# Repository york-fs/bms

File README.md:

# Battery Management System Segment Board

The distributed BMS segment board connects to a series string of 12 cells and can be queried over isolated I2C to sample
cell voltages and temperatures.

## Features

* **Isolated I2C Communication to the Master Board**
* **Accurate Voltage Measurement Using the MAX14920 Analog Frontend**
* **Passive Cell Balancing**
* **Up to 23 Connected Thermistors**
  * Three onboard thermistors around the cell balancers
  * Twenty external thermistors across two JST PUD connectors

## Cloning

A recursive clone must be used to download the `kicad-library` repository:

    git clone --recursive https://github.com/york-fs/bms-segment.git

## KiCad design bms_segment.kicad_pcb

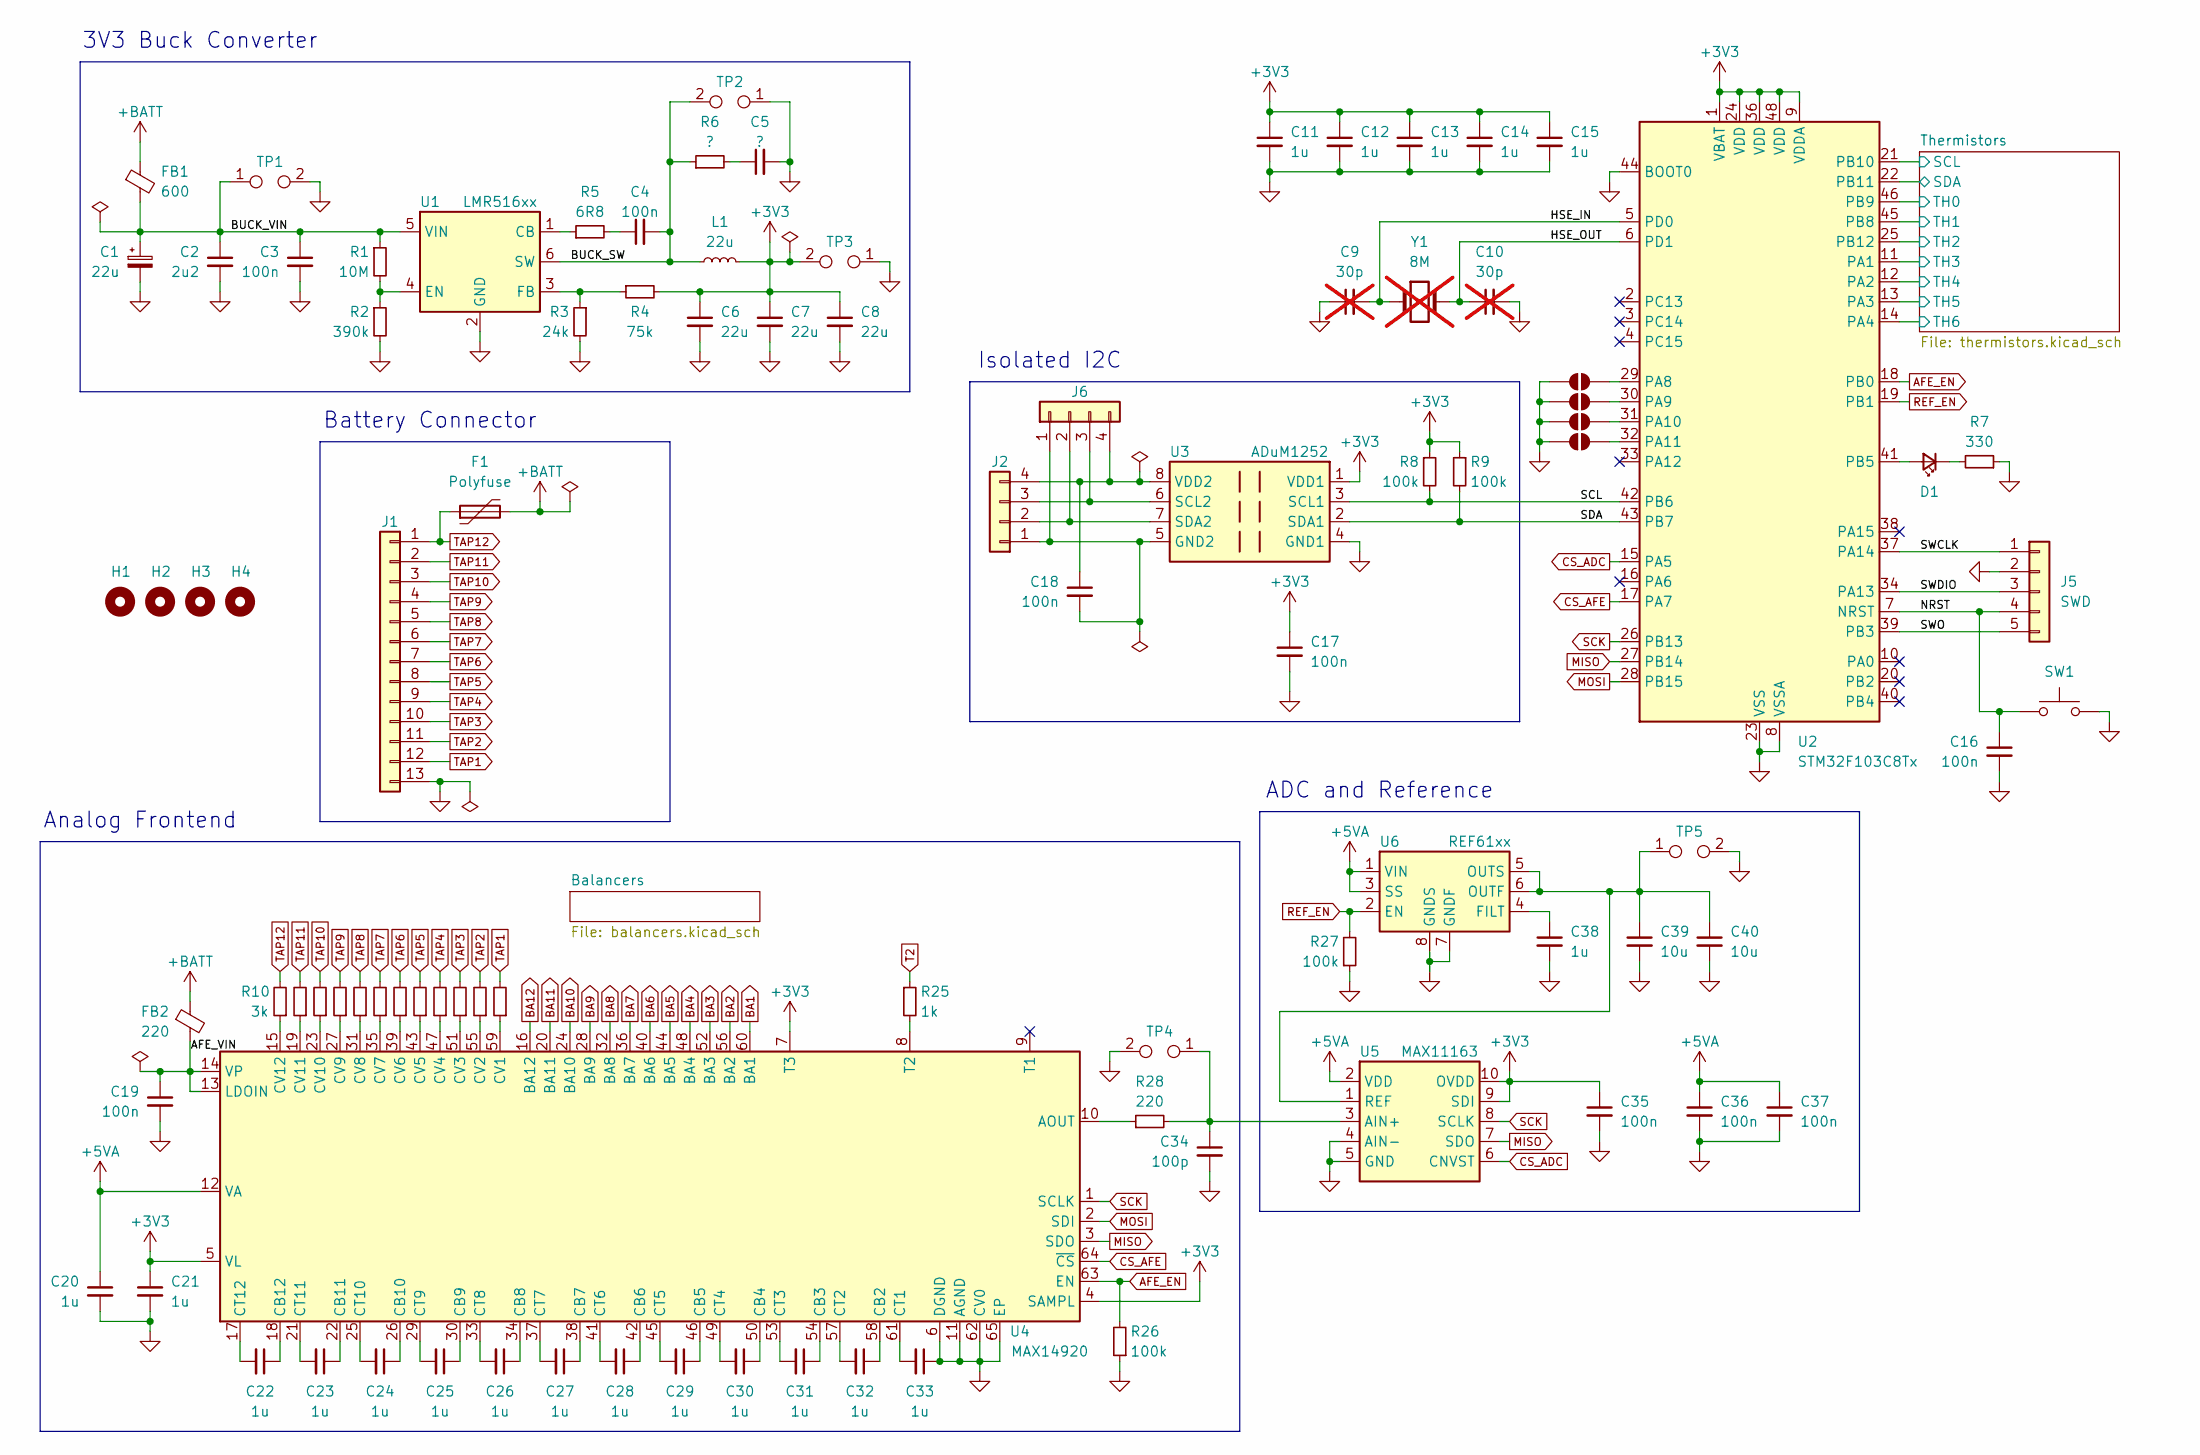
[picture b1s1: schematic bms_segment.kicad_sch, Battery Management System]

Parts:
C1: 22u; CP_Elec_6.3x7.7; Mfr # EEEFK1J220XP
C2: 2u2; C_1210_3225Metric; Mfr # GRM32ER72A225KA35
C3, C19: 100n; C_1206_3216Metric; Mfr # GRM31C5C2A104JA01L
C4, C16, C17, C18, C35, C36, C37: 100n; C_0603_1608Metric; Mfr # CL10B104KB8NNNC
C5: ?; C_0603_1608Metric
C6, C7, C8: 22u; C_1210_3225Metric; Mfr # GRM32ER71E226KE15L
C9, C10: 30p; C_0603_1608Metric; Mfr # GQM1875C2E300GB12D; not fitted
C11, C12, C13, C14, C15, C20, C21, C38: 1u; C_0603_1608Metric; Mfr # CL10B105KB8NQNC
C22, C23, C24, C25, C26, C27, C28, C29, C30, C31, C32, C33: 1u; C_0805_2012Metric; Mfr # GCM21BR71H105KA03L
C34: 100p; C_0603_1608Metric
C39, C40: 10u; C_1206_3216Metric; Mfr # GRM31CR71C106KA12L
D1: LED_Small; LED_0603_1608Metric; Mfr # NCD0603R1
F1: Polyfuse; R_1206_3216Metric; Mfr # 1206L010/60WR
FB1: 600; L_0603_1608Metric; Mfr # BLM18KG601SN1D
FB2: 220; L_0603_1608Metric; Mfr # BLM18PG221SN1D
H1, H2, H3, H4: MountingHole; MountingHole_3.2mm_M3
J1: CELL_TAPS; PhoenixContact_MC_1,5_13-G-3.81_1x13_P3.81mm_Horizontal; Mfr # MX15EDGRC-3.81-13P-GN01-Cu-A
J2, J6: I2C; JST_PH_B4B-PH-K_1x04_P2.00mm_Vertical; Mfr # B4B-PH-K-S(LF)(SN)
J5: SWD; PinHeader_1x05_P2.54mm_Vertical
JP1, JP2, JP3, JP4: SolderJumper_2_Open; SolderJumper-2_P1.3mm_Open_RoundedPad1.0x1.5mm
L1: 22u; L_Vishay_IHLP-2525; Mfr # IHLP2525CZER220M1A
R1: 10M; R_0603_1608Metric
R2: 390k; R_0603_1608Metric
R3: 24k; R_0603_1608Metric
R4: 75k; R_0603_1608Metric
R5: 6R8; R_0603_1608Metric
R6: ?; R_0603_1608Metric
R7: 330; R_0603_1608Metric; Mfr # 0603WAF3300T5E
R8, R9, R26, R27: 100k; R_0603_1608Metric; Mfr # 0603WAF1003T5E
R10, R11, R12, R13, R14, R15, R16, R17, R18, R19, R20, R21: 3k; R_0603_1608Metric; Mfr # 0603WAF3001T5E
R25: 1k; R_0603_1608Metric; Mfr # 0603WAF1001T5E
R28: 220; R_0603_1608Metric
SW1: SW_Push; SW_Push_SPST_NO_Alps_SKRK; Mfr # TS-1088-AR02016
TP1, TP2, TP3, TP4, TP5: TestPoint_2Pole; TestPoint_2Pads_Pitch2.54mm_Drill1.0mm
U1: LMR516xx; SOT-23-6; Mfr # LMR51606XDBVR
U2: STM32F103C8Tx; LQFP-48_7x7mm_P0.5mm; Mfr # STM32F103C8T6
U3: ADuM1252; MSOP-8_3x3mm_P0.65mm; Mfr # ADUM1252AUA+
U4: MAX14920; TQFP-64-1EP_10x10mm_P0.5mm_EP5.305x5.305mm; Mfr # MAX14920ECB+
U5: MAX11163; MSOP-10_3x3mm_P0.5mm; Mfr # MAX11163EUB+
U6: REF61xx; VSSOP-8_3x3mm_P0.65mm; Mfr # REF6145IDGKT
Y1: 8M; Crystal_SMD_5032-2Pin_5.0x3.2mm; Mfr # X50328MSB2GI; not fitted

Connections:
+3V3: C6.1, C7.1, C8.1, C11.1, C12.1, C13.1, C14.1, C15.1, C17.1, C21.1, C35.1, L1.2, R4.2, R8.1, R9.1, TP3.2, U2.1 (VBAT), U2.9 (VDDA), U2.24 (VDD), U2.36 (VDD), U2.48 (VDD), U3.1 (VDD1), U4.4 (SAMPL), U4.5 (VL), U4.7 (T3), U5.9 (SDI), U5.10 (OVDD); also elsewhere on the board
+5VA: C20.1, C36.1, C37.1, U4.12 (VA), U5.2 (VDD), U6.1 (VIN), U6.3 (SS)
+BATT: F1.2, FB1.1, FB2.1
/AFE_VIN: C19.1, FB2.2, U4.13 (LDOIN), U4.14 (VP)
/BUCK_SW: C4.2, L1.1, R6.1, TP2.2, U1.6 (SW)
/BUCK_VIN: C1.1, C2.1, C3.1, FB1.2, R1.1, TP1.1, U1.5 (VIN)
/HSE_IN: C9.2, U2.5 (PD0), Y1.1
/HSE_OUT: C10.1, U2.6 (PD1), Y1.2
/NRST: C16.1, J5.4, SW1.1, U2.7 (NRST)
/SCL: R8.2, U2.42 (PB6), U3.3 (SCL1)
/SDA: R9.2, U2.43 (PB7), U3.2 (SDA1)
/SWCLK: J5.1, U2.37 (PA14)
/SWDIO: J5.3, U2.34 (PA13)
/SWO: J5.5, U2.39 (PB3)
/Thermistors/SCL: U2.21 (PB10); also elsewhere on the board
/Thermistors/SDA: U2.22 (PB11); also elsewhere on the board
/Thermistors/TH0: U2.46 (PB9); also elsewhere on the board
/Thermistors/TH1: U2.45 (PB8); also elsewhere on the board
/Thermistors/TH2: U2.25 (PB12); also elsewhere on the board
/Thermistors/TH3: U2.11 (PA1); also elsewhere on the board
/Thermistors/TH4: U2.12 (PA2); also elsewhere on the board
/Thermistors/TH5: U2.13 (PA3); also elsewhere on the board
/Thermistors/TH6: U2.14 (PA4); also elsewhere on the board
AFE_EN: R26.2, U2.18 (PB0), U4.63 (EN)
BA1: U4.60 (BA1); also elsewhere on the board
BA2: U4.56 (BA2); also elsewhere on the board
BA3: U4.52 (BA3); also elsewhere on the board
BA4: U4.48 (BA4); also elsewhere on the board
BA5: U4.44 (BA5); also elsewhere on the board
BA6: U4.40 (BA6); also elsewhere on the board
BA7: U4.36 (BA7); also elsewhere on the board
BA8: U4.32 (BA8); also elsewhere on the board
BA9: U4.28 (BA9); also elsewhere on the board
BA10: U4.24 (BA10); also elsewhere on the board
BA11: U4.20 (BA11); also elsewhere on the board
BA12: U4.16 (BA12); also elsewhere on the board
CS_ADC: U2.15 (PA5), U5.6 (CNVST)
CS_AFE: U2.17 (PA7), U4.64 (~CS)
GND: C1.2, C2.2, C3.2, C5.2, C6.2, C7.2, C8.2, C9.1, C10.2, C11.2, C12.2, C13.2, C14.2, C15.2, C16.2, C17.2, C19.2, C20.2, C21.2, C33.1, C34.2, C35.2, C36.2, C37.2, C38.2, C39.2, C40.2, J1.13, J5.2, JP1.1 (A), JP2.1 (A), JP3.1 (A), JP4.1 (A), R2.2, R3.2, R7.1, R26.1, R27.1, SW1.2, TP1.2, TP2.1, TP3.1, TP4.2, TP5.2, U1.2 (GND), U2.8 (VSSA), U2.23 (VSS), U2.35 (VSS), U2.44 (BOOT0), U2.47 (VSS), U3.4 (GND1), U4.6 (DGND), U4.11 (AGND), U4.62 (CV0), U4.65 (EP), U5.4 (AIN-), U5.5 (GND), U6.7 (GNDF), U6.8 (GNDS); also elsewhere on the board
MISO: U2.27 (PB14), U4.3 (SDO), U5.7 (SDO)
MOSI: U2.28 (PB15), U4.2 (SDI)
unnamed: C4.1, R5.2
unnamed: C5.1, R6.2
unnamed: D1.2 (A), U2.41 (PB5)
unnamed: D1.1 (K), R7.2
unnamed: C18.2, J2.1, J6.1, U3.5 (GND2)
unnamed: J2.2, J6.2, U3.7 (SDA2)
unnamed: J2.3, J6.3, U3.6 (SCL2)
unnamed: C18.1, J2.4, J6.4, U3.8 (VDD2)
unnamed: JP1.2 (B), U2.29 (PA8)
unnamed: JP2.2 (B), U2.30 (PA9)
unnamed: JP3.2 (B), U2.31 (PA10)
unnamed: JP4.2 (B), U2.32 (PA11)
unnamed: R5.1, U1.1 (CB)
unnamed: R1.2, R2.1, U1.4 (EN)
unnamed: R3.1, R4.1, U1.3 (FB)
unnamed: R28.1, U4.10 (AOUT)
unnamed: C32.1, U4.58 (CB2)
unnamed: C31.1, U4.54 (CB3)
unnamed: C30.1, U4.50 (CB4)
unnamed: C29.1, U4.46 (CB5)
unnamed: C28.1, U4.42 (CB6)
unnamed: C27.1, U4.38 (CB7)
unnamed: C26.1, U4.34 (CB8)
unnamed: C25.1, U4.30 (CB9)
unnamed: C24.1, U4.26 (CB10)
unnamed: C23.1, U4.22 (CB11)
unnamed: C22.1, U4.18 (CB12)
unnamed: C33.2, U4.61 (CT1)
unnamed: C32.2, U4.57 (CT2)
unnamed: C31.2, U4.53 (CT3)
unnamed: C30.2, U4.49 (CT4)
unnamed: C29.2, U4.45 (CT5)
unnamed: C28.2, U4.41 (CT6)
unnamed: C27.2, U4.37 (CT7)
unnamed: C26.2, U4.33 (CT8)
unnamed: C25.2, U4.29 (CT9)
unnamed: C24.2, U4.25 (CT10)
unnamed: C23.2, U4.21 (CT11)
unnamed: C22.2, U4.17 (CT12)
unnamed: R21.1, U4.59 (CV1)
unnamed: R20.1, U4.55 (CV2)
unnamed: R19.1, U4.51 (CV3)
unnamed: R18.1, U4.47 (CV4)
unnamed: R17.1, U4.43 (CV5)
unnamed: R16.1, U4.39 (CV6)
unnamed: R15.1, U4.35 (CV7)
unnamed: R14.1, U4.31 (CV8)
unnamed: R13.1, U4.27 (CV9)
unnamed: R12.1, U4.23 (CV10)
unnamed: R11.1, U4.19 (CV11)
unnamed: R10.1, U4.15 (CV12)
unnamed: R25.2, U4.8 (T2)
unnamed: C34.1, R28.2, TP4.1, U5.3 (AIN+)
unnamed: C39.1, C40.1, TP5.1, U5.1 (REF), U6.5 (OUTS), U6.6 (OUTF)
unnamed: C38.1, U6.4 (FILT)
REF_EN: R27.2, U2.19 (PB1), U6.2 (EN)
SCK: U2.26 (PB13), U4.1 (SCLK), U5.8 (SCLK)
T2: R25.1; also elsewhere on the board
TAP1: J1.12, R21.2; also elsewhere on the board
TAP2: J1.11, R20.2; also elsewhere on the board
TAP3: J1.10, R19.2; also elsewhere on the board
TAP4: J1.9, R18.2; also elsewhere on the board
TAP5: J1.8, R17.2; also elsewhere on the board
TAP6: J1.7, R16.2; also elsewhere on the board
TAP7: J1.6, R15.2; also elsewhere on the board
TAP8: J1.5, R14.2; also elsewhere on the board
TAP9: J1.4, R13.2; also elsewhere on the board
TAP10: J1.3, R12.2; also elsewhere on the board
TAP11: J1.2, R11.2; also elsewhere on the board
TAP12: F1.1, J1.1, R10.2; also elsewhere on the board

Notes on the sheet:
ADC and Reference
Isolated I2C
3V3 Buck Converter
Analog Frontend
Battery Connector

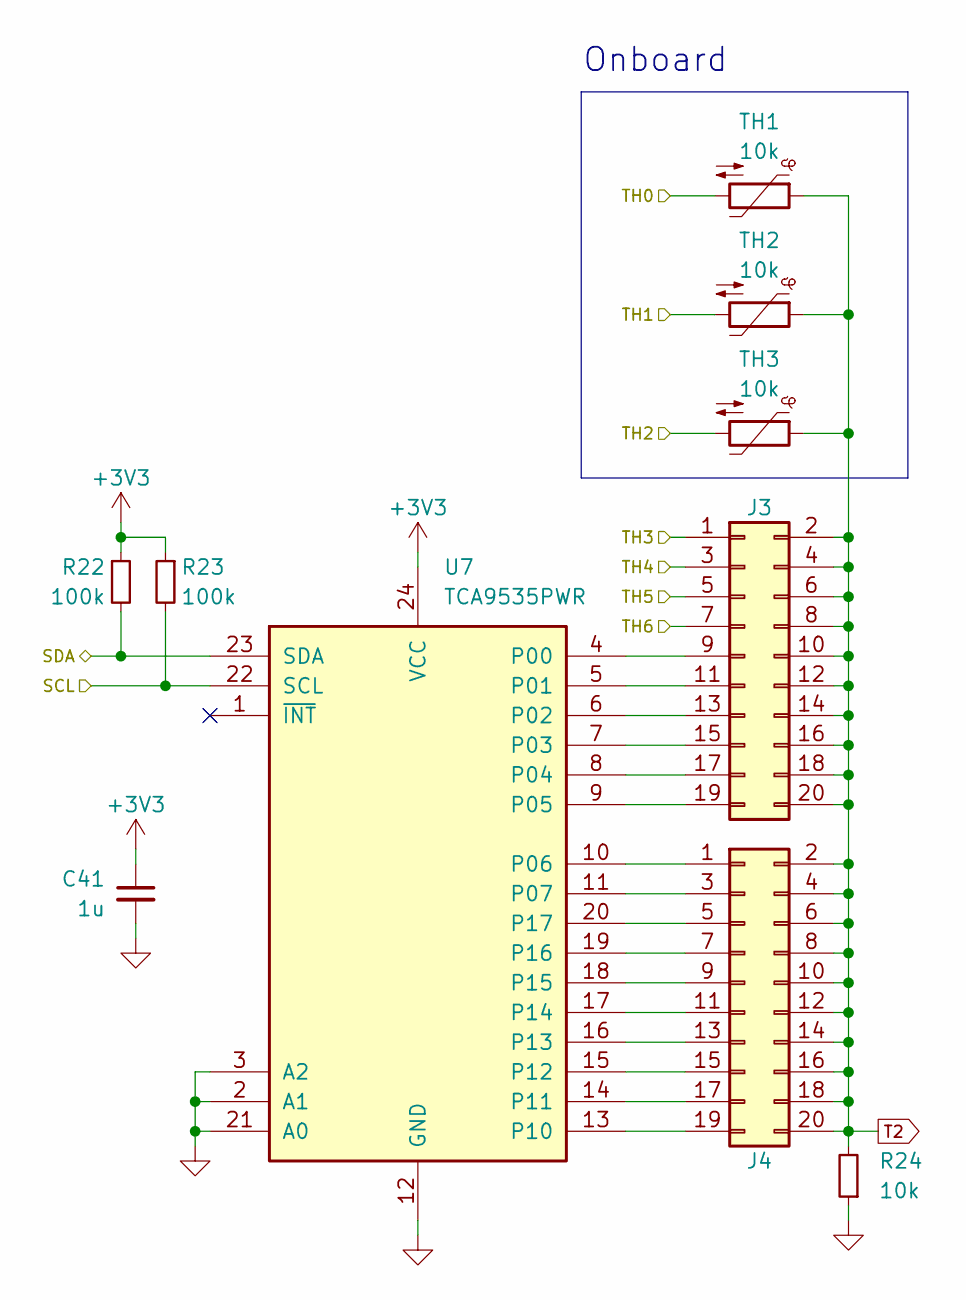
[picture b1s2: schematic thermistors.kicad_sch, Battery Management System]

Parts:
C41: 1u; C_0603_1608Metric; Mfr # CL10B105KB8NQNC
J3: THERM_1; JST_PUD_S20B-PUDSS-1_2x10_P2.00mm_Horizontal; Mfr # S20B-PUDSS-1(LF)(SN)
J4: THERM_2; JST_PUD_S20B-PUDSS-1_2x10_P2.00mm_Horizontal; Mfr # S20B-PUDSS-1(LF)(SN)
R22, R23: 100k; R_0603_1608Metric; Mfr # 0603WAF1003T5E
R24: 10k; R_0603_1608Metric; Mfr # 0603WAF1002T5E
TH1, TH2, TH3: 10k; R_0603_1608Metric; Mfr # NCP18XH103F03RB
U7: TCA9535PWR; TSSOP-24_4.4x7.8mm_P0.65mm; Mfr # TCA9535PWR

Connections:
+3V3: C41.1, R22.1, R23.1, U7.24 (VCC); also elsewhere on the board
/Thermistors/SCL: R23.2, U7.22 (SCL); also elsewhere on the board
/Thermistors/SDA: R22.2, U7.23 (SDA); also elsewhere on the board
/Thermistors/TH0: TH1.2; also elsewhere on the board
/Thermistors/TH1: TH2.2; also elsewhere on the board
/Thermistors/TH2: TH3.2; also elsewhere on the board
/Thermistors/TH3: J3.1; also elsewhere on the board
/Thermistors/TH4: J3.3; also elsewhere on the board
/Thermistors/TH5: J3.5; also elsewhere on the board
/Thermistors/TH6: J3.7; also elsewhere on the board
GND: C41.2, R24.1, U7.2 (A1), U7.3 (A2), U7.12 (GND), U7.21 (A0); also elsewhere on the board
unnamed: J3.9, U7.4 (P00)
unnamed: J3.11, U7.5 (P01)
unnamed: J3.13, U7.6 (P02)
unnamed: J3.15, U7.7 (P03)
unnamed: J3.17, U7.8 (P04)
unnamed: J3.19, U7.9 (P05)
unnamed: J4.1, U7.10 (P06)
unnamed: J4.3, U7.11 (P07)
unnamed: J4.5, U7.20 (P17)
unnamed: J4.7, U7.19 (P16)
unnamed: J4.9, U7.18 (P15)
unnamed: J4.11, U7.17 (P14)
unnamed: J4.13, U7.16 (P13)
unnamed: J4.15, U7.15 (P12)
unnamed: J4.17, U7.14 (P11)
unnamed: J4.19, U7.13 (P10)
T2: J3.2, J3.4, J3.6, J3.8, J3.10, J3.12, J3.14, J3.16, J3.18, J3.20, J4.2, J4.4, J4.6, J4.8, J4.10, J4.12, J4.14, J4.16, J4.18, J4.20, R24.2, TH1.1, TH2.1, TH3.1; also elsewhere on the board

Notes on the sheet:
Onboard

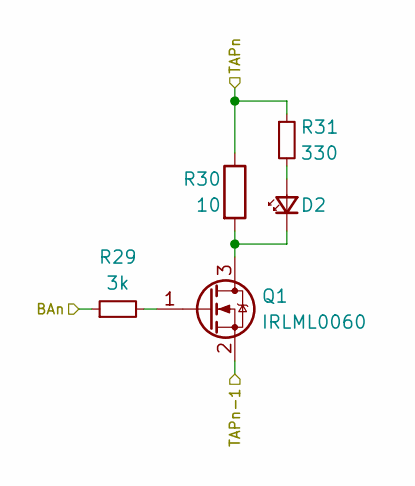
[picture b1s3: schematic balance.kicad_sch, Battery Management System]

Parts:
D2: LED_Small; LED_0603_1608Metric; Mfr # NCD0603R1
Q1: IRLML0060; SOT-23; Mfr # IRLML0060TRPBF
R29: 3k; R_0603_1608Metric; Mfr # 0603WAF3001T5E
R30: 10; R_2512_6332Metric; Mfr # RPL-12K10R0FT
R31: 330; R_0603_1608Metric; Mfr # 0603WAF3300T5E

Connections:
BA1: R29.1; also elsewhere on the board
GND: Q1.2 (S); also elsewhere on the board
unnamed: D2.2 (A), R31.2
unnamed: D2.1 (K), Q1.3 (D), R30.2
unnamed: Q1.1 (G), R29.2
TAP1: R30.1, R31.1; also elsewhere on the board

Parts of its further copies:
D3, D4, D5, D6, D7, D8, D9, D10, D11, D12, D13: LED_Small; LED_0603_1608Metric; Mfr # NCD0603R1
Q2, Q3, Q4, Q5, Q6, Q7, Q8, Q9, Q10, Q11, Q12: IRLML0060; SOT-23; Mfr # IRLML0060TRPBF
R32, R35, R38, R41, R44, R47, R50, R53, R56, R59, R62: 3k; R_0603_1608Metric; Mfr # 0603WAF3001T5E
R33, R36, R39, R42, R45, R48, R51, R54, R57, R60, R63: 10; R_2512_6332Metric; Mfr # RPL-12K10R0FT
R34, R37, R40, R43, R46, R49, R52, R55, R58, R61, R64: 330; R_0603_1608Metric; Mfr # 0603WAF3300T5E

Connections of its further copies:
BA2: R32.1; also elsewhere on the board
BA3: R35.1; also elsewhere on the board
BA4: R38.1; also elsewhere on the board
BA5: R41.1; also elsewhere on the board
BA6: R44.1; also elsewhere on the board
BA7: R47.1; also elsewhere on the board
BA8: R50.1; also elsewhere on the board
BA9: R53.1; also elsewhere on the board
BA10: R56.1; also elsewhere on the board
BA11: R59.1; also elsewhere on the board
BA12: R62.1; also elsewhere on the board
unnamed: D3.2 (A), R34.2
unnamed: D3.1 (K), Q2.3 (D), R33.2
unnamed: D4.2 (A), R37.2
unnamed: D4.1 (K), Q3.3 (D), R36.2
unnamed: D5.2 (A), R40.2
unnamed: D5.1 (K), Q4.3 (D), R39.2
unnamed: D6.2 (A), R43.2
unnamed: D6.1 (K), Q5.3 (D), R42.2
unnamed: D7.2 (A), R46.2
unnamed: D7.1 (K), Q6.3 (D), R45.2
unnamed: D8.2 (A), R49.2
unnamed: D8.1 (K), Q7.3 (D), R48.2
unnamed: D9.2 (A), R52.2
unnamed: D9.1 (K), Q8.3 (D), R51.2
unnamed: D10.2 (A), R55.2
unnamed: D10.1 (K), Q9.3 (D), R54.2
unnamed: D11.2 (A), R58.2
unnamed: D11.1 (K), Q10.3 (D), R57.2
unnamed: D12.2 (A), R61.2
unnamed: D12.1 (K), Q11.3 (D), R60.2
unnamed: D13.2 (A), R64.2
unnamed: D13.1 (K), Q12.3 (D), R63.2
unnamed: Q2.1 (G), R32.2
unnamed: Q3.1 (G), R35.2
unnamed: Q4.1 (G), R38.2
unnamed: Q5.1 (G), R41.2
unnamed: Q6.1 (G), R44.2
unnamed: Q7.1 (G), R47.2
unnamed: Q8.1 (G), R50.2
unnamed: Q9.1 (G), R53.2
unnamed: Q10.1 (G), R56.2
unnamed: Q11.1 (G), R59.2
unnamed: Q12.1 (G), R62.2
TAP1: Q2.2 (S); also elsewhere on the board
TAP2: Q3.2 (S), R33.1, R34.1; also elsewhere on the board
TAP3: Q4.2 (S), R36.1, R37.1; also elsewhere on the board
TAP4: Q5.2 (S), R39.1, R40.1; also elsewhere on the board
TAP5: Q6.2 (S), R42.1, R43.1; also elsewhere on the board
TAP6: Q7.2 (S), R45.1, R46.1; also elsewhere on the board
TAP7: Q8.2 (S), R48.1, R49.1; also elsewhere on the board
TAP8: Q9.2 (S), R51.1, R52.1; also elsewhere on the board
TAP9: Q10.2 (S), R54.1, R55.1; also elsewhere on the board
TAP10: Q11.2 (S), R57.1, R58.1; also elsewhere on the board
TAP11: Q12.2 (S), R60.1, R61.1; also elsewhere on the board
TAP12: R63.1, R64.1; also elsewhere on the board

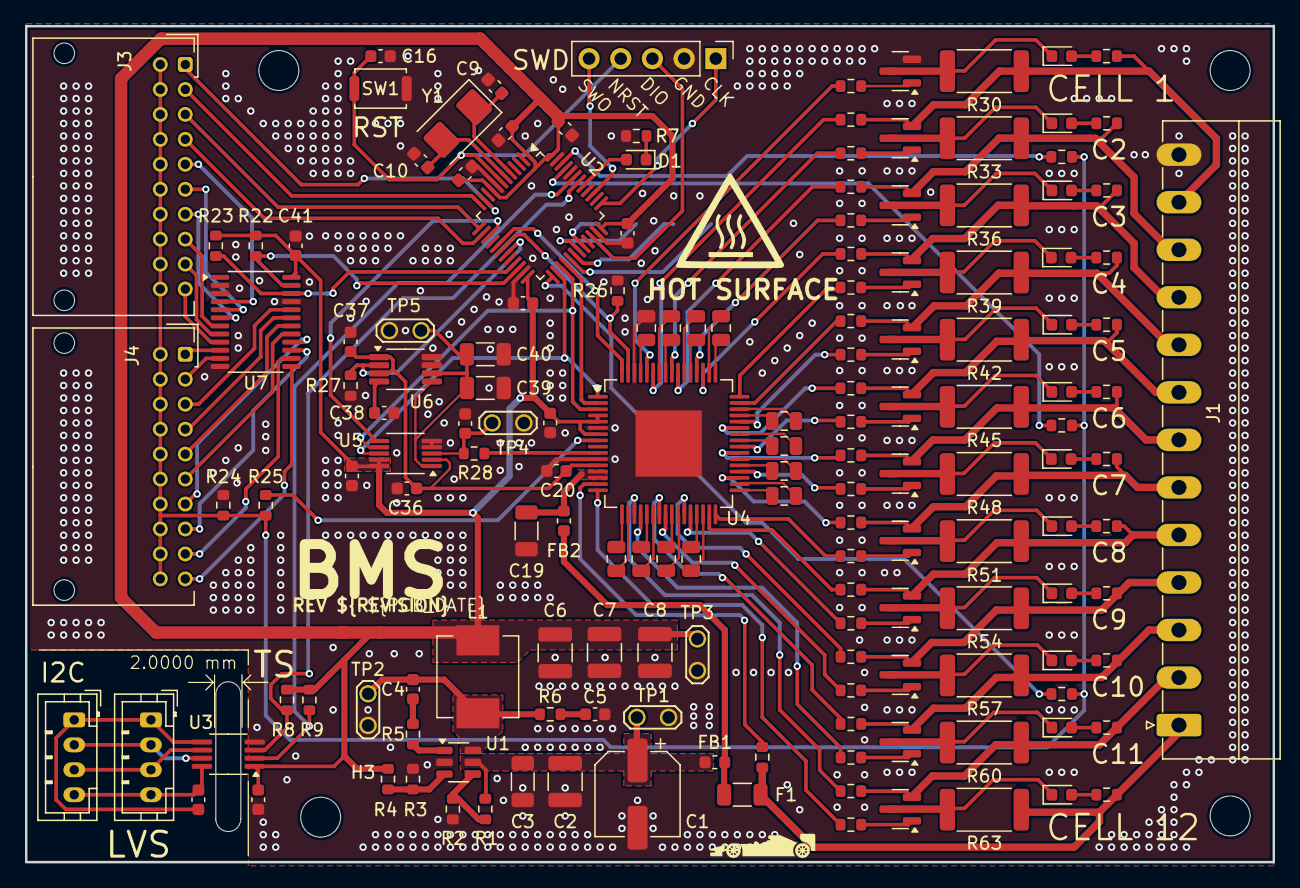
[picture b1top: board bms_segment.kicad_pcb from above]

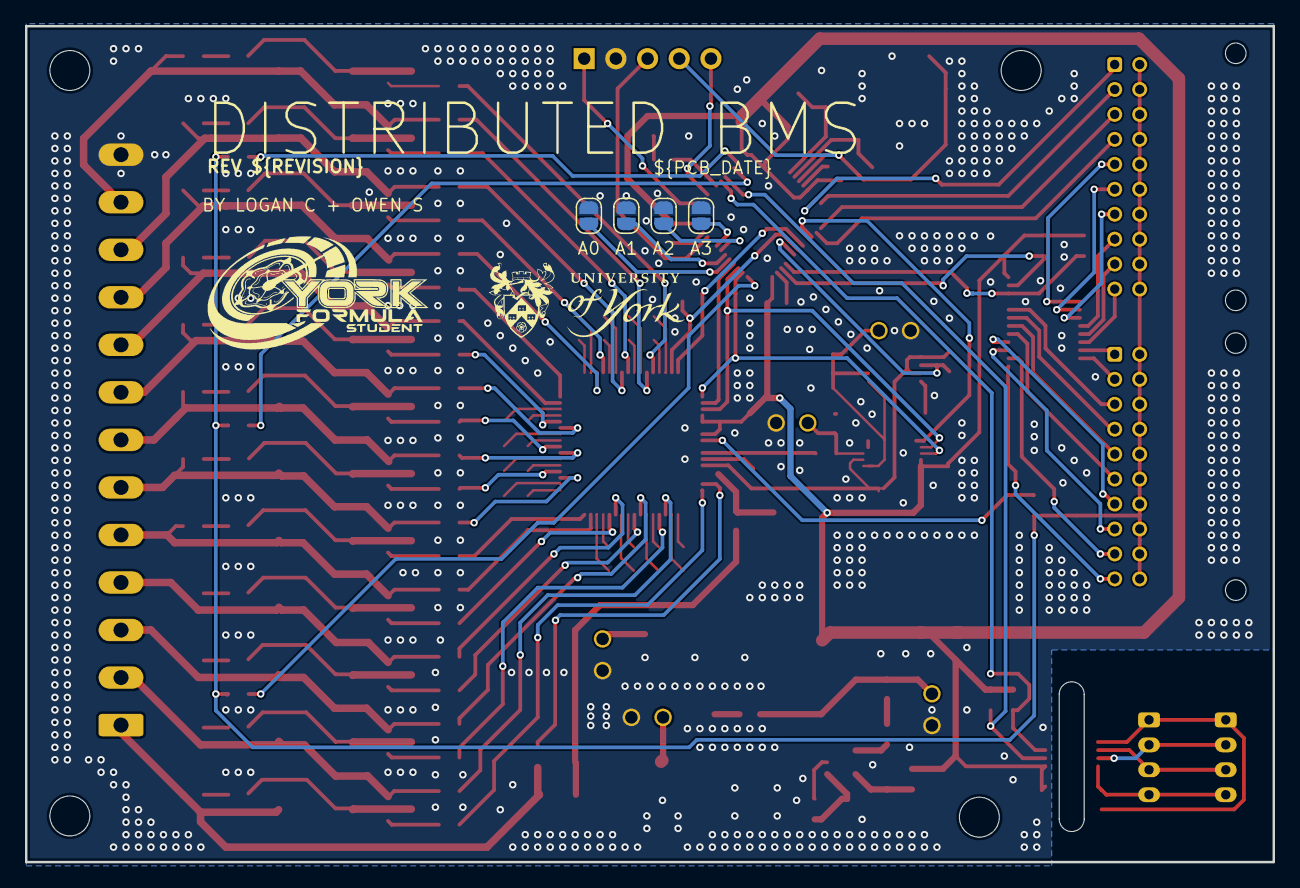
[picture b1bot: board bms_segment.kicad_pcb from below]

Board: 4 copper layers, 100.0 x 67.0 mm, 165 parts (4 on the bottom side), 163 nets.

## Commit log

2025-02-04 symbols: Add symbol for LMR51610
2025-02-04 schematic: Add buck regulator
2025-02-05 schematic: Add more output capacitors to buck converter
2025-02-05 schematic: Make buck converter 3.3 volt output
2025-02-06 schematic: Some small buck changes
2025-02-06 project: Update BOM fields
2025-02-06 symbols: Add symbols for MAX11163, MAX14920, MAX6216
2025-02-06 schematic: Lots of progress on frontend
2025-02-06 symbols: Add footprint filters for MAX11163 and MAX6216
2025-02-06 schematic: Assign some footprints
2025-02-06 schematic: Instantiate all balancers
2025-02-06 schematic: Add BOM role
2025-02-06 schematic: Add SWD header
2025-02-06 schematic: Add mounting holes
2025-02-07 schematic: Assign some more real components to passives
2025-02-07 symbols: Add symbol for ADuM1252
2025-02-07 schematic: Add isolated I2C
2025-02-08 schematic: Add thermistors
2025-02-08 schematic: MCU cleanup
2025-02-08 schematic: Assign inductor footprint and part number
2025-02-08 schematic: Fix some pin types to make ERC happy
2025-02-08 schematic: Reorder pages
2025-02-08 schematic: Add input polyfuse
2025-02-08 schematic: Add resistor to MAX14920 input
2025-02-08 schematic: Add some ferrite beads
2025-02-08 schematic: Assign remaining footprints
2025-02-08 schematic: Add some more test points
2025-02-08 schematic: Cleanup
2025-02-08 schematic: Re-annotate designators
2025-02-08 symbols: Add exposed pad pin on MAX14920
2025-02-08 pcb: Create outline
2025-02-09 schematic: Switch to 3.81 mm pitch connector for cell taps
    Also fix footprint.
2025-02-09 schematic: Add some net labels
2025-02-09 *: Adjust net classes
2025-02-09 schematic: Use smaller 2-pole test points
2025-02-18 models: Add step files for inductor and PUD connector
2025-02-18 schematic: Don't make CV12 go through fuse and adjust thermistor pinout
2025-02-18 schematic: Remove I2C_OUT connector
2025-02-18 pcb: Revert to blank PCB
2025-02-21 schematic: Reduce down to two thermistor connectors
2025-02-21 (wip) pcb: Create first PCB revision
2025-02-21 wip pcb 2
2025-02-22 schematic: Remove 1n decoupling capacitors for I2C
2025-02-22 schematic: Cleanup BOM
2025-03-03 pcb: Create first PCB revision
2025-03-03 pcb: Fill in info box
2025-03-03 pcb: Update to kicad 8.0.9
2025-03-03 pcb: Fix DRC errors and add more GND vias
2025-03-03 pcb: Set gerber output parameters
2025-03-03 pcb: Add more GND vias near reference and ADC
2025-03-03 pcb: Remove extra reference OUTS trace
2025-03-03 pcb: Cleanup tracks
2025-03-23 *: Update to kicad 9.0.0
2025-03-23 pcb: Move some close traces
2025-03-23 *: Tie AFE SAMPL pin always high
    Closes GH-2
2025-03-23 pcb: Ungroup GND vias
2025-03-23 pcb: Reduce TAP12 trace width from 1 mm to 0.6 mm
2025-03-23 pcb: Move cell tap connector towards board edge by 0.3 mm
    Closes GH-1
2025-03-23 pcb: Use a filled zone for AFE_VIN
2025-03-23 pcb: Cleanup GND vias
2025-03-23 pcb: Remove unconnected track piece
2025-03-23 pcb: Run cleanup graphics
2025-03-31 *: Remove thermistor protection zener diodes
    Closes GH-8
2025-03-31 *: Fix whitespace in BOM
2025-03-31 *: Add a pull-down on the MAX14920 enable pin
    Closes GH-13
2025-03-31 *: Change MCU LED pin
    Closes GH-3
2025-03-31 *: Mark MCU crystal as DNP
    Closes GH-6
2025-03-31 pcb: Add some more GND vias around the MCU
2025-03-31 pcb: Move cell tap connector another 0.7 mm towards the board edge
    For a total of 1 mm. Closes GH-9
2025-03-31 *: Use a more suitable footprint for the MAX14920
    This one has a more correct exposed pad size. Closes GH-4
2025-03-31 pcb: Give the vias around MAX14920 more space
2025-03-31 *: Change buck enable pin potential divider values
    Closes GH-12
2025-03-31 symbols: Add symbol for REF61xx
2025-03-31 *: Switch to the REF6145 reference
    Closes GH-7
2025-03-31 footprints: Add a 1 mm hole test point footprint
2025-03-31 *: Use new test point footprint
    Closes GH-11
2025-03-31 pcb: Fix some ground islands
2025-03-31 *: Bump revision
2025-03-31 Cleaned up silkscreen
2025-04-07 pcb: Rename AMS to BMS
2025-04-07 *: Use a variable for the revision number
    Closes GH-14
2025-04-13 pcb: Fix slightly misaligned silkscreen
2025-04-13 *: Add solder jumpers for I2C address select
2025-04-13 pcb: Improve I2C address select silkscreen
2025-04-13 pcb: Move some tracks and vias to reduce missing ground fill
2025-04-14 schematic: Update value for buck converter bootstrap resistor
2025-04-15 symbols: Add symbol for IRLML0060 MOSFET
2025-04-15 *: Use IRLML0060 for the balance MOSFETs
2025-04-15 bom: Update incorrect on-board thermistor part number
2025-04-15 symbols: Add symbol for FDV303N MOSFET
2025-04-15 *: Use FDV303N for the thermistor MOSFETs
2025-04-15 *: Use 0805 package for the sampling capacitors
    Closes GH-15
2025-04-15 *: Use two vertical JST PH connectors for I2C
2025-04-15 *: Bump to revision C
2025-05-11 *: Use a GPIO expander for the thermistors
2025-06-11 schematic: Update to new kicad symbol library
2025-06-11 pcb: Update SOT-23 footprint to latest in kicad
2025-06-11 pcb: Update remaining footprint library references
2025-06-11 pcb: Add a variable for the silkscreen date
2025-06-11 *: Tie T3 to 3V3
2025-09-28 meta: Add kicad-library submodule
2025-09-28 pcb: Update 3D model paths
2025-09-28 meta: Delete old models
2025-09-28 schematic: Update to new symbol library
2025-09-28 pcb: Update to new kicad libraries
2025-09-28 meta: Remove old symbol library
2025-09-28 *: Remove project footprint library
2025-10-05 meta: Update kicad-library and gitignore
2025-10-05 meta: Set kicad-library branch
2025-10-09 ci: Add CI
2025-10-09 meta: Add README
2025-10-11 kicad-library: Update to latest
2025-10-13 meta: Rename project to bms-segment
2025-10-19 meta: Add .lck files to gitignore
2025-10-20 bom: Remove spaces from part numbers
